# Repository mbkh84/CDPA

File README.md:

# CDPA
Class-D Power Amplifier

Self-oscillating Class-D power amplifier.
The control mode is voltage-mode.

The PCB software is Autodesk Eagle.

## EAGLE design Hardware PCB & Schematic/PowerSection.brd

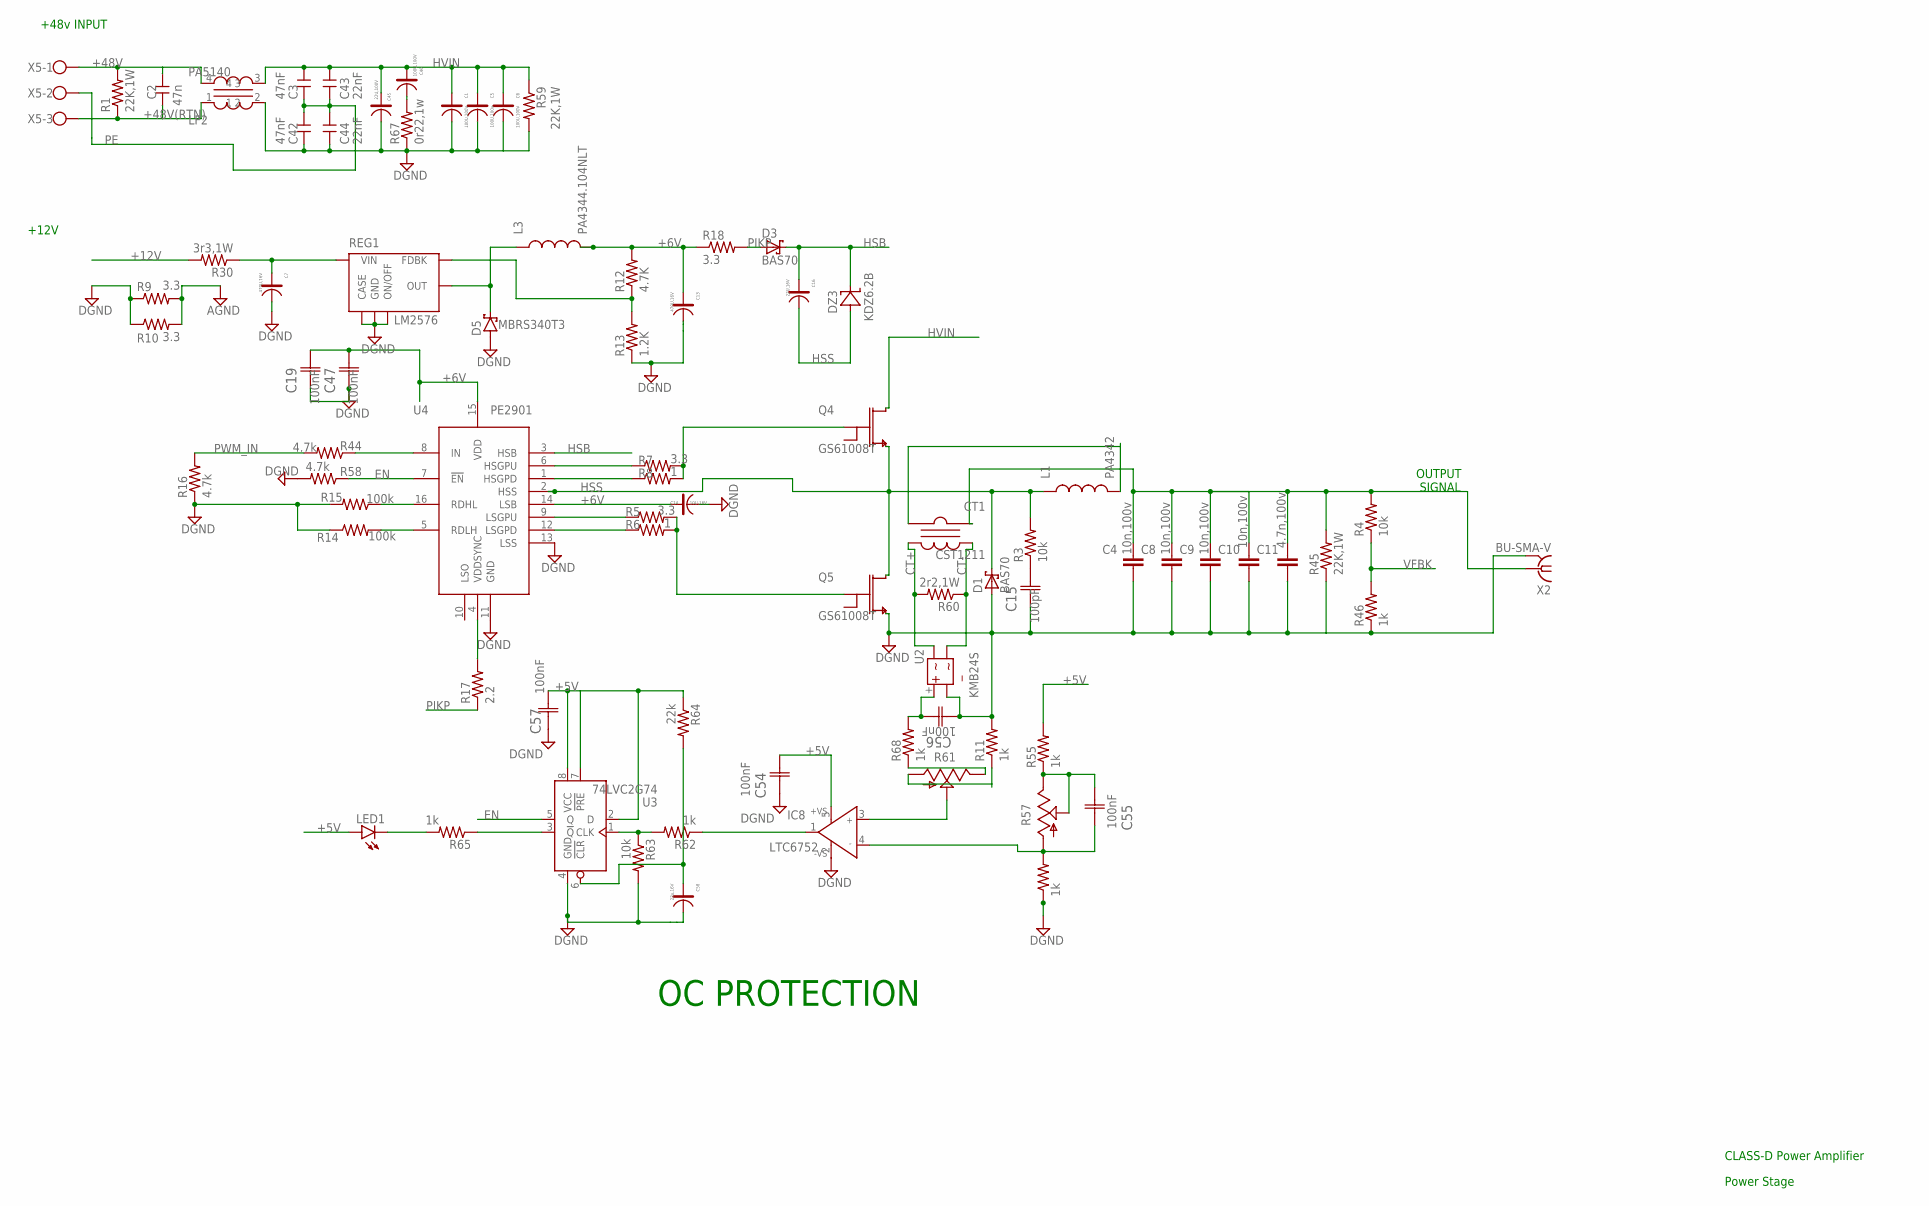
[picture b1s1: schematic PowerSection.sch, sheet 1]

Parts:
C1, C6, C46: 100U,100V; CEL-EDH-9R
C2: 47n; 2220
C3, C42: 47nF; 2220
C4, C8, C9, C10: 10n,100v; C2220K
C5: 100U,100v; CEL-EDH-9R
C7, C13: 470U,16V; CEL-EDH-9P
C11: 4.7n,100v; C2225K
C14: 10U-16V; CEL-EDK-9B
C15: 100pF; CAPC3216X88N
C16: 22U,16V; CEL-EDK-9D
C19, C47, C54, C55, C56, C57: 100nF; CAPC3216X88N
C43, C44: 22nF; 2220
C45: 22U,100V; CEL-EDH-9M
C58: 22u,16V; CEL-EDK-9D
CT1: CST1211
D1, D3: BAS70; SOT23
D5: MBRS340T3; SMC
DZ3: KDZ6.2B; SOD123FL
IC8: LTC6752; SOT23-5
L1: PA4342
L3: PA4344.104NLT; 104NLT
LED1: LEDCHIPLED_1206; CHIPLED_1206
LF2: PA5140; PA5140.XXXNL
Q4, Q5: GS61008T; 61008T
R1, R45, R59: 22K,1W; R2512W
R3, R4, R63: 10k; R1206
R5, R7, R9, R10, R18: 3.3; R1206
R6, R8: 1; R1206
R11, R46, R55, R56, R62, R65, R68: 1k; R1206
R12: 4.7K; R1206
R13: 1.2K; R1206
R14, R15: 100k; R1206
R16, R44, R58: 4.7k; R1206
R17: 2.2; R1206
R30: 3r3,1W; R2512W
R57, R61: TRIM_US-3223G; 3223G
R60: 2r2,1W; R2512W
R64: 22k; R1206
R67: 0r22,1w; R2512W
REG1: LM2576; TO263-5
U2: KMB24S; SOIC-4
U3: 74LVC2G74; SOT765
U4: PE2901; BGA20C40P5X4_164X204X28
X2: BU-SMA-V
X5: W237-103

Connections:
+5V: C54.2 (C2), C57.2 (C2), IC8.5 (+VS), LED1.A, R55.2, R64.1, U3.2 (D), U3.7 (!PRE), U3.8 (VCC); also elsewhere on the board
+6V: C13.1, C14.1, C19.2 (C2), C47.2 (C2), L3.2, R12.2, R18.1, U4.14 (LSB), U4.15 (VDD)
+12V: R30.2; also elsewhere on the board
+48V: C2.2, LF2.4, R1.2, X5.1; also elsewhere on the board
+48V(RTN): C2.1, LF2.1, R1.1, X5.3; also elsewhere on the board
AGND: R9.2, R10.2; also elsewhere on the board
CT+: CT1.4 (V_-), R60.2, U2.~2 (2)
CT-: CT1.5 (V_+), R60.1, U2.~1 (1)
DGND: C1.2, C4.2, C5.2, C6.2, C7.2, C8.2, C9.2, C10.2, C11.2, C13.2, C14.2, C15.1 (C1), C19.1 (C1), C42.1, C44.1, C45.2, C47.1 (C1), C54.1 (C1), C56.1 (C1), C57.1 (C1), C58.2, D1.1 (A), D5.A, IC8.2 (-VS), LF2.2, Q5.3, R9.1, R10.1, R11.2, R13.1, R14.1, R15.2, R16.1, R45.1, R46.1, R56.1, R58.2, R59.2, R63.2, R67.1, REG1.3 (GND), REG1.5 (ON/OFF), REG1.6 (CASE), U2.- (4), U3.4 (GND), U4.11 (GND), U4.13 (LSS), X2.2, X2.3 (2), X2.4 (2), X2.5 (2); also elsewhere on the board
EN: R58.1, U3.5 (Q), U4.7 (!EN!)
HSB: C16.1, D3.3 (K), DZ3.C, U4.3 (HSB)
HSS: C16.2, D1.3 (K), DZ3.A, L1.P$1 (1), Q4.3, Q5.1, R3.2, U4.2 (HSS)
HVIN: C1.1, C3.2, C5.1, C6.1, C43.2, C45.1, C46.1, LF2.3, Q4.1, R59.1
unnamed: R61.3 (E), R68.1
unnamed: C4.1, C8.1, C9.1, C10.1, C11.1, CT1.1 (C_IN), R4.2, R45.2, X2.1
unnamed: C15.2 (C2), R3.1
unnamed: C7.1, R30.1, REG1.1 (VIN)
unnamed: R12.1, R13.2, REG1.4 (FDBK)
unnamed: D5.C, L3.1, REG1.2 (OUT)
unnamed: R44.1, U4.8 (IN)
unnamed: R11.1, R61.1 (A)
unnamed: R15.1, U4.16 (RDHL)
unnamed: R17.2, U4.4 (VDDSYNC)
unnamed: R7.1, U4.6 (HSGPU)
unnamed: R8.1, U4.1 (HSGPD)
unnamed: R5.1, U4.9 (LSGPU)
unnamed: R6.1, U4.12 (LSGPD)
unnamed: CT1.2 (C_OUT), L1.P$2 (2)
unnamed: Q5.2, R5.2, R6.2
unnamed: C56.2 (C2), R68.2, U2.+ (3)
unnamed: C46.2, R67.2
unnamed: R14.2, U4.5 (RDLH)
unnamed: Q4.2, R7.2, R8.2
unnamed: C55.1 (C1), IC8.4 (IN-), R56.2, R57.1 (A)
unnamed: IC8.3 (IN+), R61.2 (S)
unnamed: IC8.1 (OUT), R62.1
unnamed: C55.2 (C2), R55.1, R57.2 (S), R57.3 (E)
unnamed: R62.2, R63.1, U3.1 (CLK)
unnamed: LED1.C, R65.2
unnamed: C58.1, R64.2, U3.6 (!CLR)
unnamed: R65.1, U3.3 (!Q)
PE: C3.1, C42.2, C43.1, C44.2, X5.2; also elsewhere on the board
PIKP: D3.1 (A), R17.1, R18.2
PWM_IN: R16.2, R44.2; also elsewhere on the board
VFBK: R4.1, R46.2; also elsewhere on the board

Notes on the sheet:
Power Stage
CLASS-D Power Amplifier
+48v INPUT
+12V
OUTPUT SIGNAL
OC PROTECTION

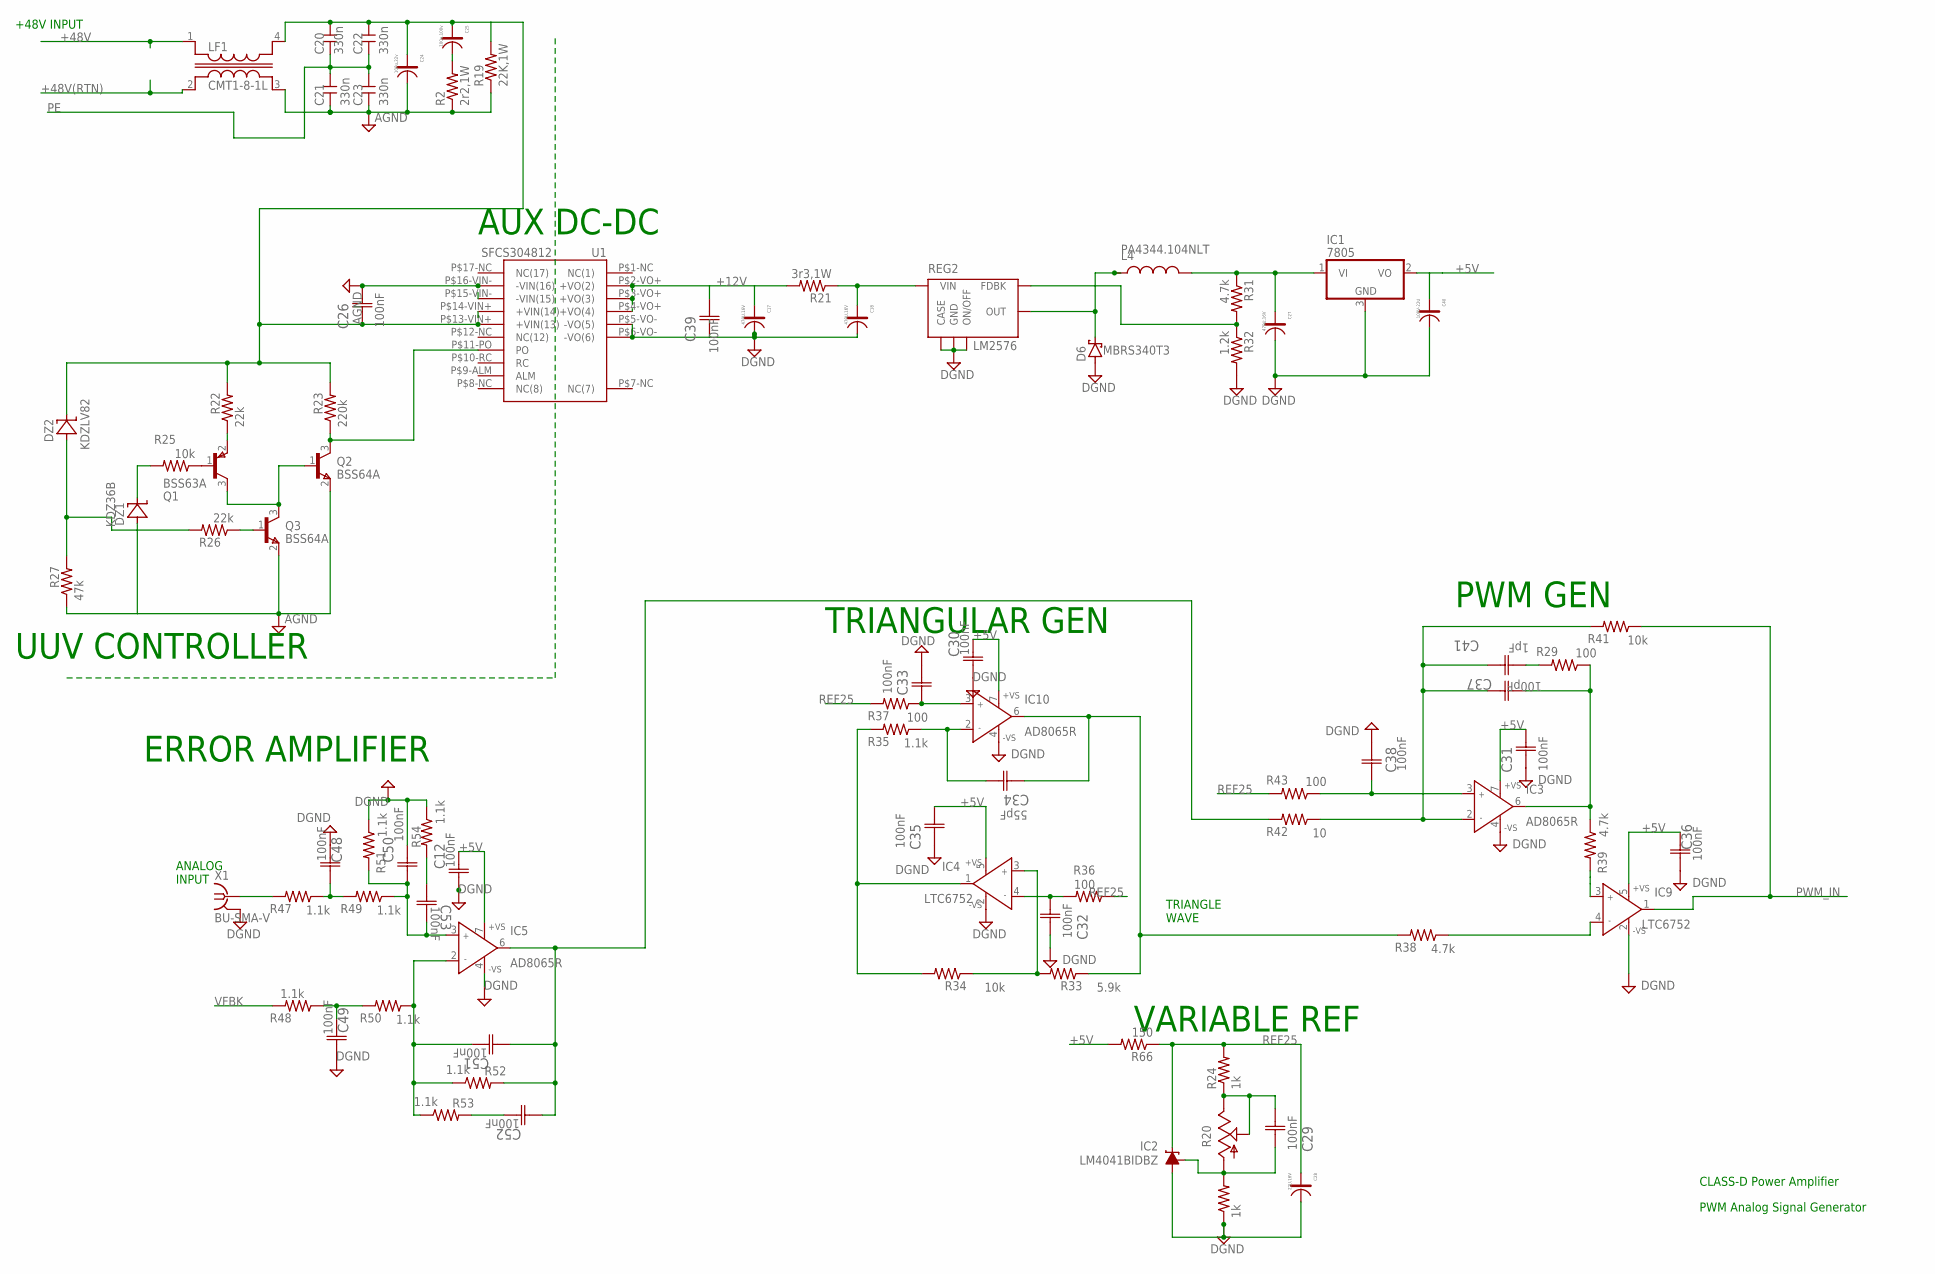
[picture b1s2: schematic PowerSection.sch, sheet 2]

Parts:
C12, C26, C29, C30, C31, C32, C33, C35, C36, C38, C39, C48, C49, C50, C51, C52, C53: 100nF; CAPC3216X88N
C17, C18, C27: 470U,16V; CEL-EDH-9P
C20, C21, C22, C23: 330n; 2220
C24: 100u,22v; CEL-EDH-9M
C25: 100u,100v; CEL-EDH-9R
C28: 22U,16V; CEL-EDK-9D
C34: 55pF; CAPC3216X88N
C37: 100pF; CAPC3216X88N
C40: 100V-22U; CEL-EDH-9M
C41: 1pF; CAPC3216X88N
D6: MBRS340T3; SMC
DZ1: KDZ36B; SOD123FL
DZ2: KDZLV82; SOD123FL
IC1: 7805; TO252
IC2: LM4041BIDBZ; DBZ_R-PDSO-G3
IC3, IC5, IC10: AD8065R; SO8
IC4, IC9: LTC6752; SOT23-5
L4: PA4344.104NLT; 104NLT
LF1: CMT1-8-1L
Q1: BSS63A; SOT23
Q2, Q3: BSS64A; SOT23
R2: 2r2,1W; R2512W
R19: 22K,1W; R2512W
R20: TRIM_US-3223G; 3223G
R21: 3r3,1W; R2512W
R22, R26: 22k; R1206
R23: 220k; R1206
R24, R28: 1k; R1206
R25, R34, R41: 10k; R1206
R27: 47k; R1206
R29, R36, R37, R43: 100; R1206
R31, R38, R39: 4.7k; R1206
R32: 1.2k; R1206
R33: 5.9k; R1206
R35, R47, R48, R49, R50, R51, R52, R53, R54: 1.1k; R1206
R42: 10; R1206
R66: 150; R1206
REG2: LM2576; TO263-5
U1: SFCS304812; SFCS_SMD
X1: BU-SMA-V

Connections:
+5V: C12.2 (C2), C30.2 (C2), C31.2 (C2), C35.2 (C2), C36.2 (C2), C40.1, IC1.2 (VO), IC3.7 (+VS), IC4.5 (+VS), IC5.7 (+VS), IC9.5 (+VS), IC10.7 (+VS), R66.2; also elsewhere on the board
+12V: C17.1, C39.2 (C2), R21.2, U1.P$2-VO+ (+VO(2)), U1.P$3-VO+ (+VO(3)), U1.P$4-VO+ (+VO(4)); also elsewhere on the board
+48V: LF1.1; also elsewhere on the board
+48V(RTN): LF1.2; also elsewhere on the board
AGND: C21.1, C23.1, C24.2, C26.2 (C2), DZ1.A, LF1.3, Q2.2 (E), Q3.2 (E), R2.1, R19.1, R27.1, U1.P$16-VIN- (-VIN(16)); also elsewhere on the board
DGND: C12.1 (C1), C17.2, C18.2, C27.2, C28.2, C30.1 (C1), C31.1 (C1), C32.1 (C1), C33.2 (C2), C35.1 (C1), C36.1 (C1), C38.2 (C2), C39.1 (C1), C40.2, C48.2 (C2), C49.1 (C1), C50.2 (C2), D6.A, IC1.3 (GND), IC2.3 (A), IC3.4 (-VS), IC4.2 (-VS), IC5.4 (-VS), IC9.2 (-VS), IC10.4 (-VS), R28.1, R32.2, R51.1, R54.1, REG2.3 (GND), REG2.5 (ON/OFF), REG2.6 (CASE), U1.P$5-VO- (-VO(5)), U1.P$6-VO- (-VO(6)), X1.2, X1.3 (2), X1.4 (2), X1.5 (2); also elsewhere on the board
unnamed: C25.2, R2.2
unnamed: R47.2, X1.1
unnamed: C48.1 (C1), R47.1, R49.2
unnamed: C50.1 (C1), C53.2 (C2), IC5.3 (IN+), R49.1, R51.2
unnamed: C20.2, C22.2, C24.1, C25.1, C26.1 (C1), DZ2.C, LF1.4, R19.2, R22.2, R23.2, U1.P$13-VIN+ (+VIN(13))
unnamed: Q1.1 (B), R25.1
unnamed: C18.1, R21.1, REG2.1 (VIN)
unnamed: Q1.2 (E), R22.1
unnamed: Q2.3 (C), R23.1, U1.P$11-PO (PO)
unnamed: DZ1.C, R25.2
unnamed: DZ2.A, R26.2, R27.2
unnamed: Q3.1 (B), R26.1
unnamed: R31.2, R32.1, REG2.4 (FDBK)
unnamed: D6.C, L4.1, REG2.2 (OUT)
unnamed: C32.2 (C2), IC4.4 (IN-), R36.2
unnamed: C33.1 (C1), IC10.3 (IN+), R37.1
unnamed: C34.2 (C2), IC10.2 (IN-), R35.1
unnamed: C34.1 (C1), IC10.6 (OUT), R33.1, R38.2
unnamed: IC9.4 (IN-), R38.1
unnamed: C51.1 (C1), C52.1 (C1), IC5.6 (OUT), R42.2, R52.2
unnamed: C37.2 (C2), C41.2 (C2), IC3.2 (IN-), R41.2, R42.1
unnamed: IC4.3 (IN+), R33.2, R34.1
unnamed: IC4.1 (OUT), R34.2, R35.2
unnamed: Q1.3 (C), Q2.1 (B), Q3.3 (C)
unnamed: C29.2 (C2), R20.2 (S), R20.3 (E), R24.1
unnamed: C38.1 (C1), IC3.3 (IN+), R43.1
unnamed: IC9.3 (IN+), R39.2
unnamed: C37.1 (C1), IC3.6 (OUT), R29.1, R39.1
unnamed: C27.1, IC1.1 (VI), L4.2, R31.1
unnamed: C29.1 (C1), IC2.1 (FB), R20.1 (A), R28.2
unnamed: C41.1 (C1), R29.2
unnamed: C51.2 (C2), IC5.2 (IN-), R50.1, R52.1, R53.1
unnamed: C49.2 (C2), R48.1, R50.2
unnamed: C53.1 (C1), R54.2
unnamed: C52.2 (C2), R53.2
PE: C20.1, C21.2, C22.1, C23.2; also elsewhere on the board
PWM_IN: IC9.1 (OUT), R41.1; also elsewhere on the board
REF25: C28.1, IC2.2 (C), R24.2, R36.1, R37.2, R43.2, R66.1
VFBK: R48.2; also elsewhere on the board

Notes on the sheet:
CLASS-D Power Amplifier
PWM Analog Signal Generator
TRIANGLE WAVE
+48V INPUT
ANALOG INPUT
ERROR AMPLIFIER
UUV CONTROLLER
AUX DC-DC
TRIANGULAR GEN
VARIABLE REF
PWM GEN

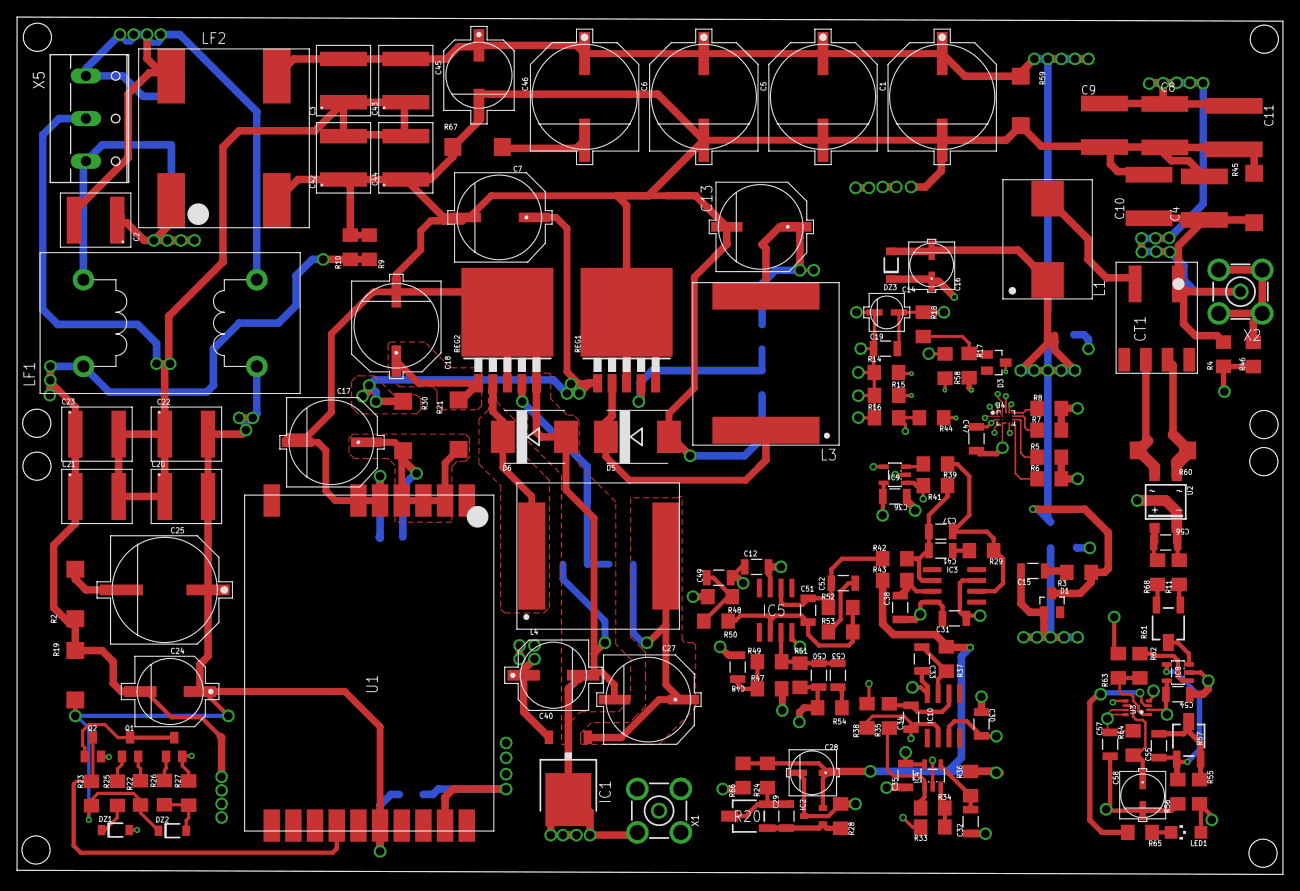
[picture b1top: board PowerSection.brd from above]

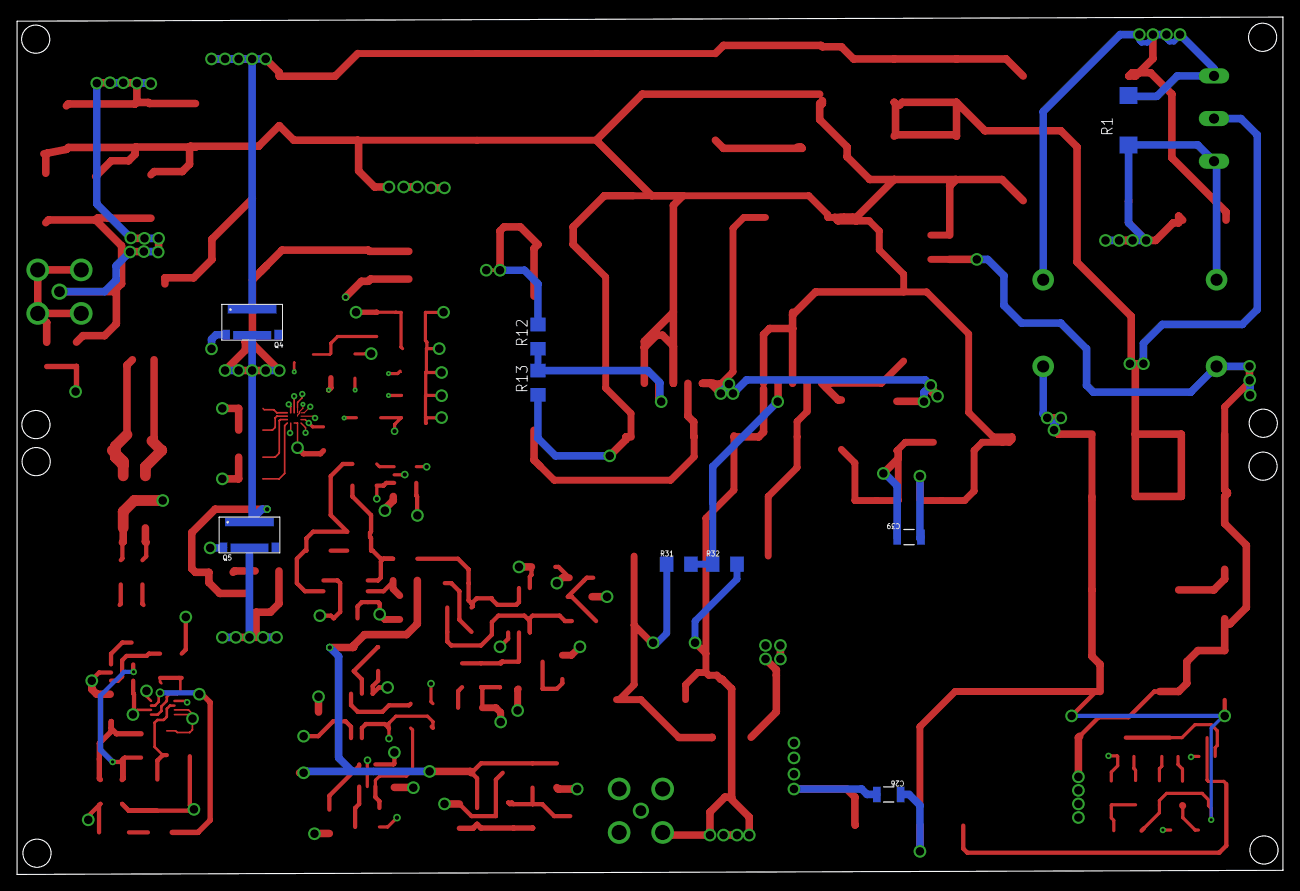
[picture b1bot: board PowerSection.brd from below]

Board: 6 copper layers, 148.4 x 100.5 mm, 161 parts (9 on the bottom side), 81 nets.

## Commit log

2021-02-26 Sch&PCB
2021-02-27 Thesis Document
